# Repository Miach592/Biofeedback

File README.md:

View this project on [CADLAB.io](https://cadlab.io/project/1697). 

# Biofeedback

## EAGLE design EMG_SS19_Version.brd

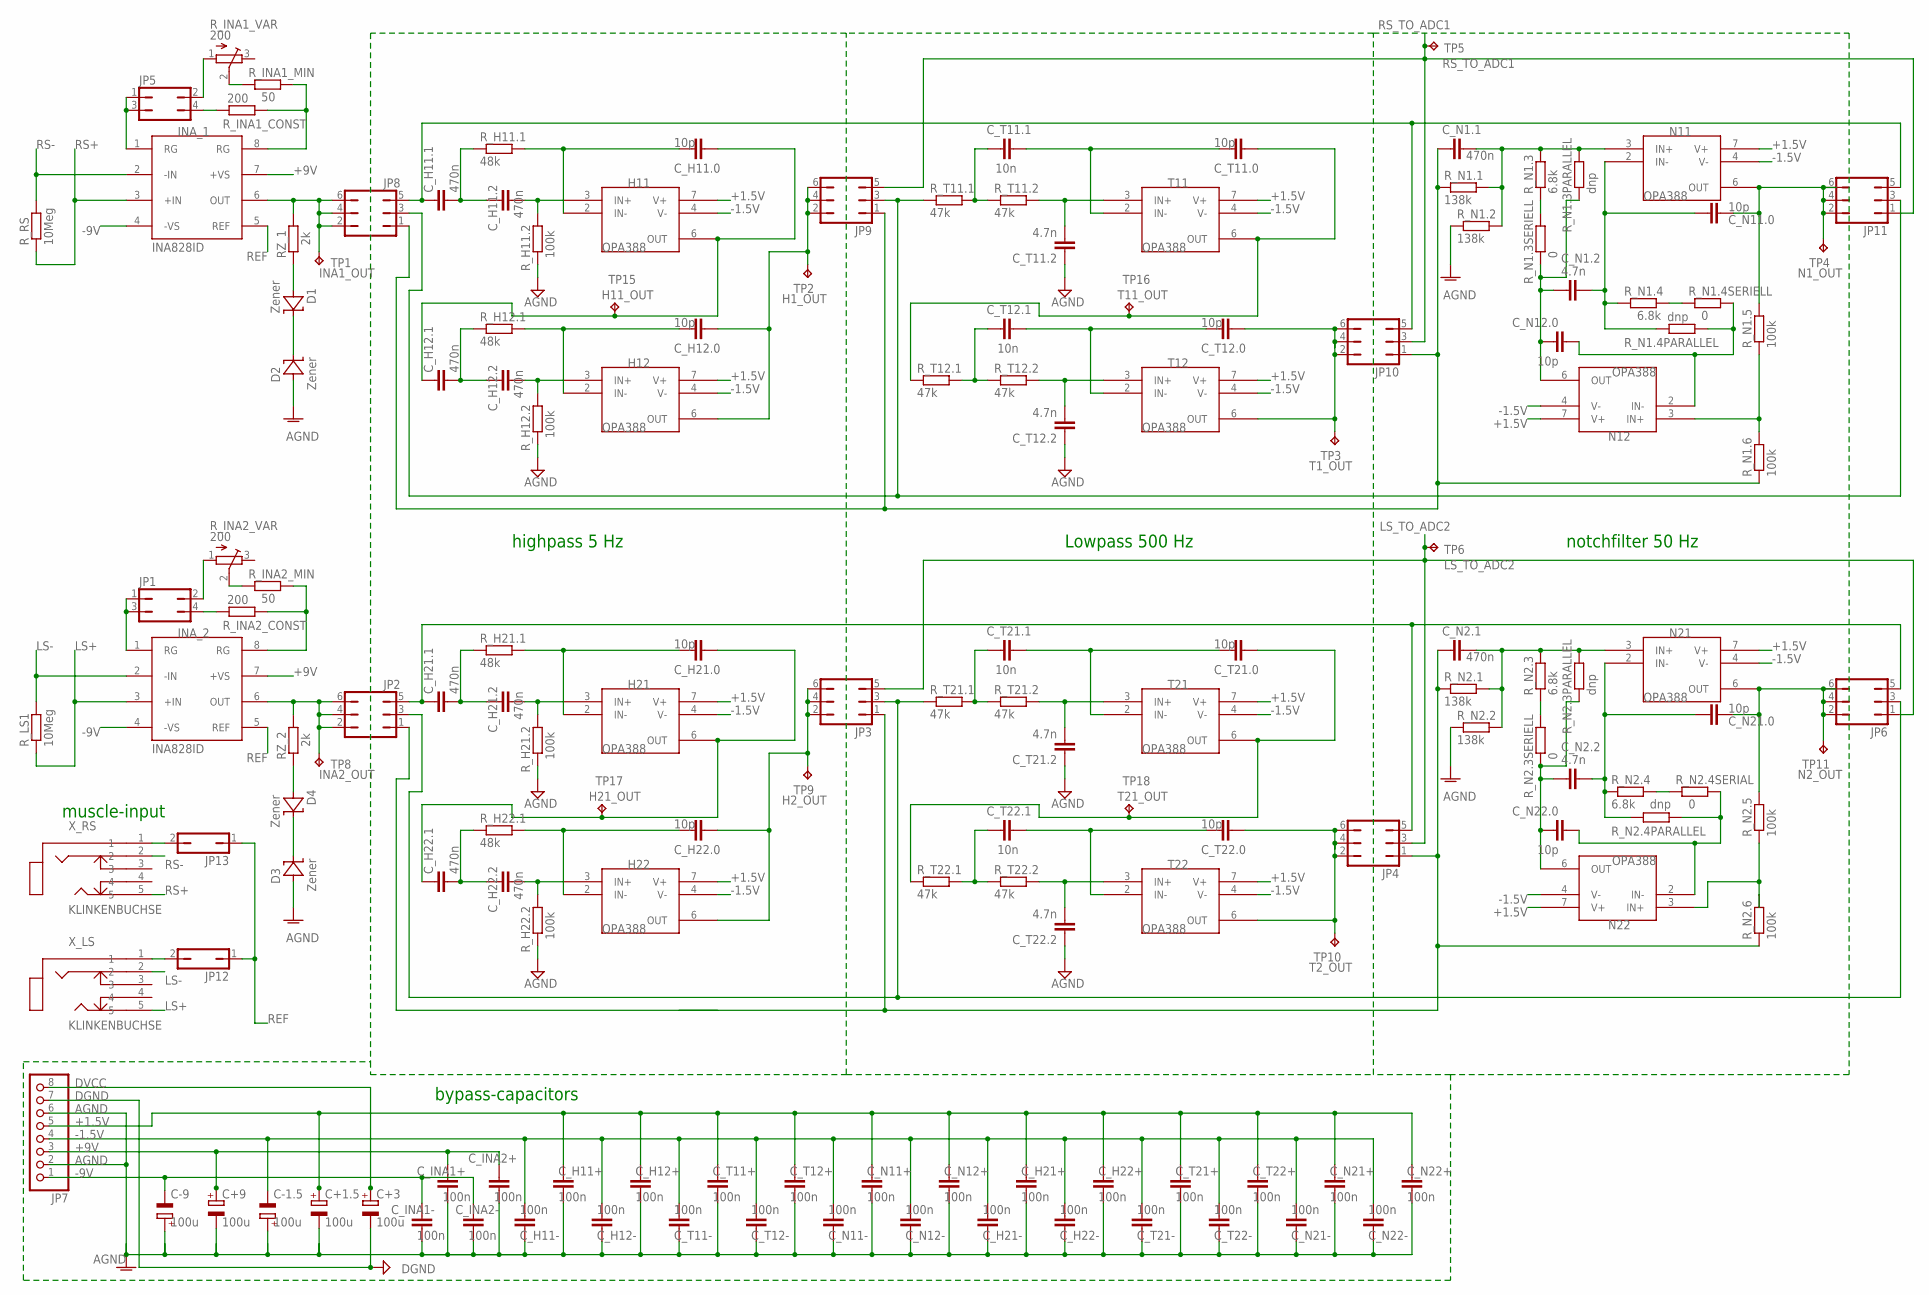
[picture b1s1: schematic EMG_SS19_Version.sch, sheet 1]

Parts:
C+1.5, C+3, C+9: 100u; RADIAL_SMD_ELKO_6_3
C-1.5, C-9: 100u; RADIAL_SMD_ELKO_6_3
C_H11+, C_H11-, C_H12+, C_H12-, C_H21+, C_H21-, C_H22+, C_H22-: 100n; C0805
C_H11.0, C_H12.0, C_H21.0, C_H22.0: 10p; C0805
C_H11.1, C_H11.2, C_H12.1, C_H12.2, C_H21.1, C_H21.2, C_H22.1, C_H22.2: 470n; C0805
C_INA1+, C_INA1-, C_INA2+, C_INA2-: 100n; C0805
C_N1.1, C_N2.1: 470n; C0805
C_N1.2, C_N2.2: 4.7n; C0805
C_N11+, C_N11-, C_N12+, C_N12-, C_N21+, C_N21-, C_N22+, C_N22-: 100n; C0805
C_N11.0, C_N12.0, C_N21.0, C_N22.0: 10p; C0805
C_T11+, C_T11-, C_T12+, C_T12-, C_T21+, C_T21-, C_T22+, C_T22-: 100n; C0805
C_T11.0, C_T12.0, C_T21.0, C_T22.0: 10p; C0805
C_T11.1, C_T12.1, C_T21.1, C_T22.1: 10n; C0805
C_T11.2, C_T12.2, C_T21.2, C_T22.2: 4.7n; C0805
D1, D2, D3, D4: Zener; SOT-23
H11, H12, H21, H22: OPA388; SOIC127P600X175-8N
INA_1, INA_2: INA828ID; SOIC8
JP1, JP5: JP2Q
JP2, JP3, JP4, JP6, JP8, JP9, JP10, JP11: JP3Q
JP7: PINHD-1X8; 1X08
JP12, JP13: JP1Q; JP1
N11, N12, N21, N22: OPA388; SOIC127P600X175-8N
RZ_1, RZ_2: 2k; R0805
R_H11.1, R_H12.1, R_H21.1, R_H22.1: 48k; R0805
R_H11.2, R_H12.2, R_H21.2, R_H22.2: 100k; R0805
R_INA1_CONST, R_INA2_CONST: 200; R0805
R_INA1_MIN, R_INA2_MIN: 50; R0805
R_INA1_VAR, R_INA2_VAR: 200; SM-42/43W
R_LS1: 10Meg; R0805
R_N1.1, R_N1.2, R_N2.1, R_N2.2: 138k; R0805
R_N1.3, R_N1.4, R_N2.3, R_N2.4: 6.8k; R0805
R_N1.3PARALLEL, R_N1.4PARALLEL, R_N2.3PARALLEL, R_N2.4PARALLEL: dnp; R0805
R_N1.3SERIELL, R_N1.4SERIELL, R_N2.3SERIELL, R_N2.4SERIAL: 0; R0805
R_N1.5, R_N1.6, R_N2.5, R_N2.6: 100k; R0805
R_RS: 10Meg; R0805
R_T11.1, R_T11.2, R_T12.1, R_T12.2, R_T21.1, R_T21.2, R_T22.1, R_T22.2: 47k; R0805
T11, T12, T21, T22: OPA388; SOIC127P600X175-8N
TP1, TP2, TP3, TP4, TP8, TP9, TP10, TP11, TP15, TP16, TP17, TP18: TPPAD1-13; P1-13
TP5: RS_TO_ADC; P1-13
TP6: LS_TO_ADC; P1-13
X_LS: KLINKENBUCHSE; FC68131-5P
X_RS: KLINKENBUCHSE; FC68131-5P

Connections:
+1.5V: C+1.5.+, C_H11+.1, C_H12+.1, C_H21+.1, C_H22+.1, C_N11+.1, C_N12+.1, C_N21+.1, C_N22+.1, C_T11+.1, C_T12+.1, C_T21+.1, C_T22+.1, H11.7 (V+), H12.7 (V+), H21.7 (V+), H22.7 (V+), JP7.5, N11.7 (V+), N12.7 (V+), N21.7 (V+), N22.7 (V+), T11.7 (V+), T12.7 (V+), T21.7 (V+), T22.7 (V+)
+9V: C+9.+, C_INA1+.1, C_INA2+.1, INA_1.7 (+VS), INA_2.7 (+VS), JP7.3
-1.5V: C-1.5.-, C_H11-.2, C_H12-.2, C_H21-.2, C_H22-.2, C_N11-.2, C_N12-.2, C_N21-.2, C_N22-.2, C_T11-.2, C_T12-.2, C_T21-.2, C_T22-.2, H11.4 (V-), H12.4 (V-), H21.4 (V-), H22.4 (V-), JP7.4, N11.4 (V-), N12.4 (V-), N21.4 (V-), N22.4 (V-), T11.4 (V-), T12.4 (V-), T21.4 (V-), T22.4 (V-)
-9V: C-9.-, C_INA1-.1, C_INA2-.1, INA_1.4 (-VS), INA_2.4 (-VS), JP7.1
AGND: C+1.5.-, C+9.-, C-1.5.+, C-9.+, C_H11+.2, C_H11-.1, C_H12+.2, C_H12-.1, C_H21+.2, C_H21-.1, C_H22+.2, C_H22-.1, C_INA1+.2, C_INA1-.2, C_INA2+.2, C_INA2-.2, C_N11+.2, C_N11-.1, C_N12+.2, C_N12-.1, C_N21+.2, C_N21-.1, C_N22+.2, C_N22-.1, C_T11+.2, C_T11-.1, C_T11.2.1, C_T12+.2, C_T12-.1, C_T12.2.1, C_T21+.2, C_T21-.1, C_T21.2.1, C_T22+.2, C_T22-.1, C_T22.2.1, D2.1 (A), D3.1 (A), JP7.2, JP7.6, R_H11.2.1, R_H12.2.1, R_H21.2.1, R_H22.2.1, R_N1.2.1, R_N2.2.1; also elsewhere on the board
DGND: C+3.-, JP7.7; also elsewhere on the board
DVCC: C+3.+, JP7.8; also elsewhere on the board
H1_OUT: C_H12.0.1, H12.6 (OUT), JP9.2, JP9.4, JP9.6, TP2.TP
H2_OUT: C_H22.0.1, H22.6 (OUT), JP3.2, JP3.4, JP3.6, TP9.TP
H11_OUT: C_H11.0.1, C_H12.1.1, H11.6 (OUT), TP15.TP
H21_OUT: C_H21.0.1, C_H22.1.1, H21.6 (OUT), TP17.TP
INA1_OUT: INA_1.6 (OUT), JP8.2, JP8.4, JP8.6, RZ_1.2, TP1.TP
INA2_OUT: INA_2.6 (OUT), JP2.2, JP2.4, JP2.6, RZ_2.2, TP8.TP
LS+: INA_2.3 (+IN), R_LS1.1, X_LS.5
LS-: INA_2.2 (-IN), R_LS1.2, X_LS.2
LS_TO_ADC2: JP3.5, JP4.3, JP6.1, TP6.TP; also elsewhere on the board
N1_OUT: C_N11.0.1, JP11.2, JP11.4, JP11.6, N11.6 (OUT), R_N1.5.2, TP4.TP
N2_OUT: C_N21.0.1, JP6.2, JP6.4, JP6.6, N21.6 (OUT), R_N2.5.2, TP11.TP
unnamed: R_INA2_MIN.1, R_INA2_VAR.2 (S)
unnamed: C_H11.1.2, C_H11.2.1, R_H11.1.1
unnamed: C_H11.2.2, H11.3 (IN+), R_H11.2.2
unnamed: D1.1 (A), RZ_1.1
unnamed: D1.3 (C), D2.3 (C)
unnamed: C_H12.1.2, C_H12.2.1, R_H12.1.1
unnamed: C_H12.2.2, H12.3 (IN+), R_H12.2.2
unnamed: C_T11.1.1, R_T11.1.2, R_T11.2.1
unnamed: C_H11.0.2, H11.2 (IN-), R_H11.1.2
unnamed: C_T11.2.2, R_T11.2.2, T11.3 (IN+)
unnamed: C_T12.1.1, R_T12.1.2, R_T12.2.1
unnamed: C_H12.0.2, H12.2 (IN-), R_H12.1.2
unnamed: C_T12.2.2, R_T12.2.2, T12.3 (IN+)
unnamed: C_T12.0.2, C_T12.1.2, T12.2 (IN-)
unnamed: JP5.4, R_INA1_CONST.1
unnamed: C_N1.1.2, N11.3 (IN+), R_N1.1.2, R_N1.2.2, R_N1.3.2, R_N1.3PARALLEL.2
unnamed: C_N1.2.1, C_N12.0.2, N12.6 (OUT), R_N1.3PARALLEL.1, R_N1.3SERIELL.1
unnamed: C_N1.2.2, C_N11.0.2, N11.2 (IN-), R_N1.4.1, R_N1.4PARALLEL.1
unnamed: C_N12.0.1, N12.2 (IN-), R_N1.4PARALLEL.2, R_N1.4SERIELL.2
unnamed: C_T11.0.2, C_T11.1.2, T11.2 (IN-)
unnamed: N12.3 (IN+), R_N1.5.1, R_N1.6.2
unnamed: C_H21.1.2, C_H21.2.1, R_H21.1.1
unnamed: C_H21.2.2, H21.3 (IN+), R_H21.2.2
unnamed: C_H22.1.2, C_H22.2.1, R_H22.1.1
unnamed: C_H22.2.2, H22.3 (IN+), R_H22.2.2
unnamed: C_T21.1.1, R_T21.1.2, R_T21.2.1
unnamed: C_T21.2.2, R_T21.2.2, T21.3 (IN+)
unnamed: C_T22.1.1, R_T22.1.2, R_T22.2.1
unnamed: C_T22.2.2, R_T22.2.2, T22.3 (IN+)
unnamed: C_N2.1.2, N21.3 (IN+), R_N2.1.2, R_N2.2.2, R_N2.3.2, R_N2.3PARALLEL.2
unnamed: C_N2.2.1, C_N22.0.2, N22.6 (OUT), R_N2.3PARALLEL.1, R_N2.3SERIELL.1
unnamed: C_N2.2.2, C_N21.0.2, N21.2 (IN-), R_N2.4.1, R_N2.4PARALLEL.1
unnamed: C_N22.0.1, N22.2 (IN-), R_N2.4PARALLEL.2, R_N2.4SERIAL.2
unnamed: N22.3 (IN+), R_N2.5.1, R_N2.6.2
unnamed: JP1.4, R_INA2_CONST.1
unnamed: JP1.2, R_INA2_VAR.1 (A)
unnamed: JP5.2, R_INA1_VAR.1 (A)
unnamed: C_H21.1.1, JP2.5, JP4.5, JP6.5
unnamed: C_H11.1.1, JP8.5, JP10.5, JP11.5
unnamed: JP2.3, JP3.3, JP6.3, R_T21.1.1
unnamed: C_N2.1.1, JP2.1, JP3.1, JP4.1, R_N2.1.1, R_N2.6.1
unnamed: JP8.3, JP9.3, JP11.3, R_T11.1.1
unnamed: C_N1.1.1, JP8.1, JP9.1, JP10.1, R_N1.1.1, R_N1.6.1
unnamed: D4.1 (A), RZ_2.1
unnamed: D3.3 (C), D4.3 (C)
unnamed: C_H21.0.2, H21.2 (IN-), R_H21.1.2
unnamed: R_INA1_MIN.1, R_INA1_VAR.2 (S)
unnamed: C_H22.0.2, H22.2 (IN-), R_H22.1.2
unnamed: C_T22.0.2, C_T22.1.2, T22.2 (IN-)
unnamed: C_T21.0.2, C_T21.1.2, T21.2 (IN-)
unnamed: JP12.2, X_LS.1
unnamed: JP13.2, X_RS.1
unnamed: R_N2.4.2, R_N2.4SERIAL.1
unnamed: R_N2.3.1, R_N2.3SERIELL.2
unnamed: R_N1.3.1, R_N1.3SERIELL.2
unnamed: R_N1.4.2, R_N1.4SERIELL.1
REF: INA_1.5 (REF), INA_2.5 (REF), JP12.1, JP13.1
RG1+: INA_1.1 (RG), JP5.1, JP5.3
RG1-: INA_1.8 (RG), R_INA1_CONST.2, R_INA1_MIN.2
RG2+: INA_2.1 (RG), JP1.1, JP1.3
RG2-: INA_2.8 (RG), R_INA2_CONST.2, R_INA2_MIN.2
RS+: INA_1.3 (+IN), R_RS.1, X_RS.5
RS-: INA_1.2 (-IN), R_RS.2, X_RS.2
RS_TO_ADC1: JP9.5, JP10.3, JP11.1, TP5.TP; also elsewhere on the board
T1_OUT: C_T12.0.1, JP10.2, JP10.4, JP10.6, T12.6 (OUT), TP3.TP
T2_OUT: C_T22.0.1, JP4.2, JP4.4, JP4.6, T22.6 (OUT), TP10.TP
T11_OUT: C_T11.0.1, R_T12.1.1, T11.6 (OUT), TP16.TP
T21_OUT: C_T21.0.1, R_T22.1.1, T21.6 (OUT), TP18.TP

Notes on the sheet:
highpass 5 Hz
Lowpass 500 Hz
notchfilter 50 Hz
bypass-capacitors
muscle-input

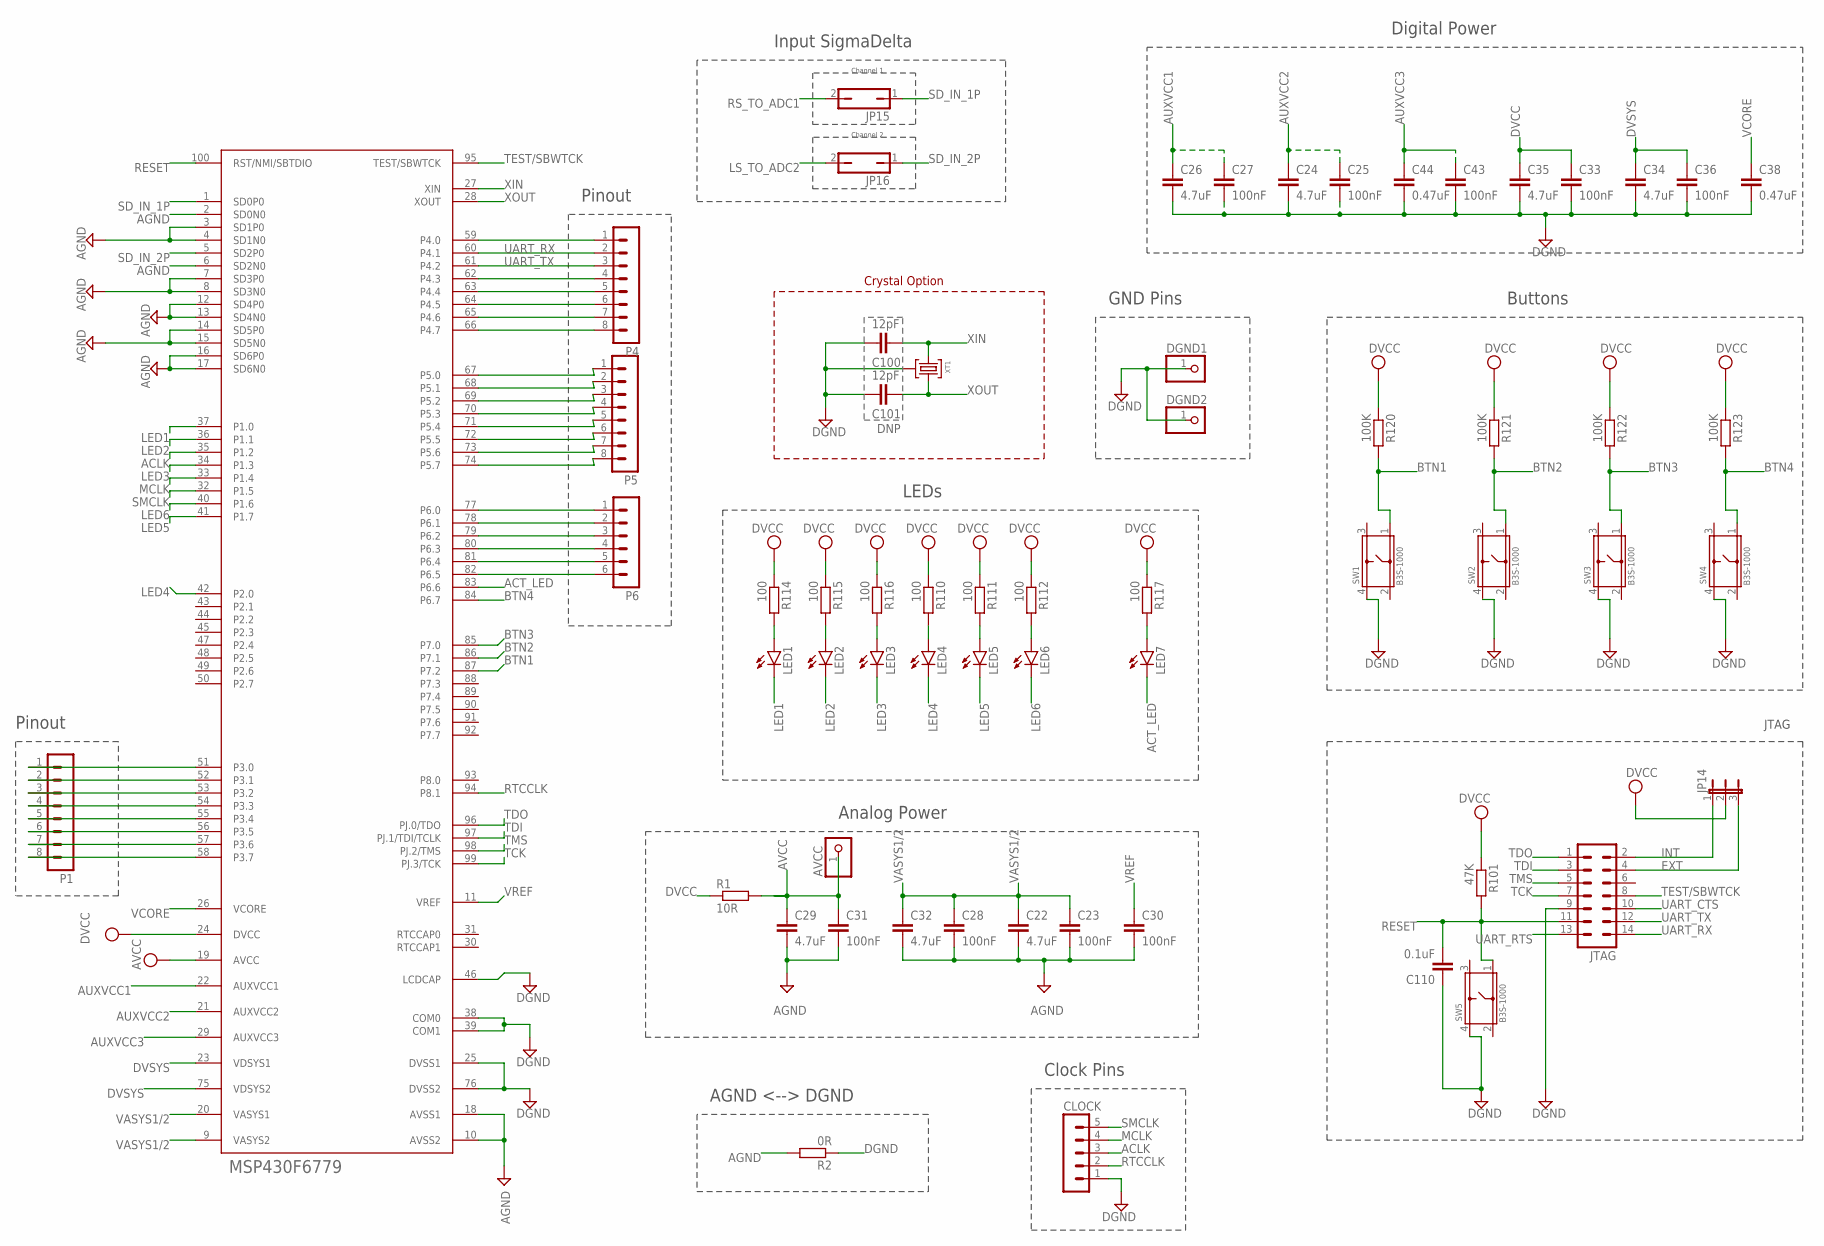
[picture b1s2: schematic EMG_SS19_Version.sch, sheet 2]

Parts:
AVCC: PINHD-1X1; 1X01
C22, C24, C26, C29, C32, C34, C35: 4.7uF; C0805
C23, C25, C27, C28, C30, C31, C33, C36, C43: 100nF; C0805
C38, C44: 0.47uF; C0805
C100, C101: 12pF; C0805
C110: 0.1uF; C0805
CLOCK: MA05-1
DGND1, DGND2: PINHD-1X1; 1X01
JP14: JP2E; JP2
JP15, JP16: JP1Q; JP1
JTAG: ML14
LED1, LED2, LED3, LED4, LED5, LED6, LED7: LEDCHIP-LED0805; CHIP-LED0805
P1, P4, P5: MA08-1
P6: MA06-1
R1: 10R; R0805
R2: 0R; R0805
R101: 47K; R0805
R110, R111, R112, R114, R115, R116, R117: 100; R0805
R120, R121, R122, R123: 100K; R0805
SW1, SW2, SW3, SW4, SW5: B3S-1000; SW_B3S-1000
U$1: MSP430F6779PZ; S-PQFP-G100(PZ)
XT1: CM200T

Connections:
ACLK: CLOCK.3, U$1.35 (P1.2)
ACT_LED: LED7.C, U$1.83 (P6.6)
AGND: C22.2, C23.2, C28.2, C29.2, C30.2, C31.2, C32.2, R2.2, U$1.2 (SD0N0), U$1.3 (SD1P0), U$1.4 (SD1N0), U$1.6 (SD2N0), U$1.7 (SD3P0), U$1.8 (SD3N0), U$1.10 (AVSS2), U$1.12 (SD4P0), U$1.13 (SD4N0), U$1.14 (SD5P0), U$1.15 (SD5N0), U$1.16 (SD6P0), U$1.17 (SD6N0), U$1.18 (AVSS1); also elsewhere on the board
AUXVCC1: C26.1, C27.1, U$1.22 (AUXVCC1)
AUXVCC2: C24.1, C25.1, U$1.21 (AUXVCC2)
AUXVCC3: C43.1, C44.1, U$1.29 (AUXVCC3)
AVCC: AVCC.1, C29.1, C31.1, R1.2, U$1.19 (AVCC)
BTN1: R120.2, SW1.1, U$1.87 (P7.2)
BTN2: R121.2, SW2.1, U$1.86 (P7.1)
BTN3: R122.2, SW3.1, U$1.85 (P7.0)
BTN4: R123.2, SW4.1, U$1.84 (P6.7)
DGND: C24.2, C25.2, C26.2, C27.2, C33.2, C34.2, C35.2, C36.2, C38.2, C43.2, C44.2, C100.2, C101.2, C110.1, CLOCK.1, DGND1.1, DGND2.1, JTAG.9, R2.1, SW1.4, SW2.4, SW3.4, SW4.4, SW5.4, U$1.25 (DVSS1), U$1.38 (COM0), U$1.39 (COM1), U$1.46 (LCDCAP), U$1.76 (DVSS2), XT1.P3 (3); also elsewhere on the board
DVCC: C33.1, C35.1, JP14.2, R1.1, R101.1, R110.1, R111.1, R112.1, R114.1, R115.1, R116.1, R117.1, R120.1, R121.1, R122.1, R123.1, U$1.24 (DVCC); also elsewhere on the board
DVSYS: C34.1, C36.1, U$1.23 (VDSYS1), U$1.75 (VDSYS2)
EXT: JP14.3, JTAG.4
INT: JP14.1, JTAG.2
LED1: LED1.C, U$1.37 (P1.0)
LED2: LED2.C, U$1.36 (P1.1)
LED3: LED3.C, U$1.34 (P1.3)
LED4: LED4.C, U$1.42 (P2.0)
LED5: LED5.C, U$1.41 (P1.7)
LED6: LED6.C, U$1.40 (P1.6)
LS_TO_ADC2: JP16.2; also elsewhere on the board
MCLK: CLOCK.4, U$1.33 (P1.4)
unnamed: LED1.A, R114.2
unnamed: LED2.A, R115.2
unnamed: LED3.A, R116.2
unnamed: LED7.A, R117.2
unnamed: LED4.A, R110.2
unnamed: LED5.A, R111.2
unnamed: LED6.A, R112.2
unnamed: P1.1, U$1.51 (P3.0)
unnamed: P1.2, U$1.52 (P3.1)
unnamed: P1.3, U$1.53 (P3.2)
unnamed: P1.4, U$1.54 (P3.3)
unnamed: P1.5, U$1.55 (P3.4)
unnamed: P1.6, U$1.56 (P3.5)
unnamed: P1.7, U$1.57 (P3.6)
unnamed: P1.8, U$1.58 (P3.7)
unnamed: P5.1, U$1.67 (P5.0)
unnamed: P5.2, U$1.68 (P5.1)
unnamed: P5.3, U$1.69 (P5.2)
unnamed: P5.4, U$1.70 (P5.3)
unnamed: P5.5, U$1.71 (P5.4)
unnamed: P5.6, U$1.72 (P5.5)
unnamed: P5.7, U$1.73 (P5.6)
unnamed: P5.8, U$1.74 (P5.7)
unnamed: P4.5, U$1.63 (P4.4)
unnamed: P6.2, U$1.78 (P6.1)
unnamed: P6.1, U$1.77 (P6.0)
P4.0: P4.1, U$1.59 (P4.0)
P4.3: P4.4, U$1.62 (P4.3)
P4.5: P4.6, U$1.64 (P4.5)
P4.6: P4.7, U$1.65 (P4.6)
P4.7: P4.8, U$1.66 (P4.7)
P6.2: P6.3, U$1.79 (P6.2)
P6.3: P6.4, U$1.80 (P6.3)
P6.4: P6.5, U$1.81 (P6.4)
P6.5: P6.6, U$1.82 (P6.5)
RESET: C110.2, JTAG.11, R101.2, SW5.1, U$1.100 (RST/NMI/SBTDIO)
RS_TO_ADC1: JP15.2; also elsewhere on the board
RTCCLK: CLOCK.2, U$1.94 (P8.1)
SD_IN_1P: JP15.1, U$1.1 (SD0P0)
SD_IN_2P: JP16.1, U$1.5 (SD2P0)
SMCLK: CLOCK.5, U$1.32 (P1.5)
TCK: JTAG.7, U$1.99 (PJ.3/TCK)
TDI: JTAG.3, U$1.97 (PJ.1/TDI/TCLK)
TDO: JTAG.1, U$1.96 (PJ.0/TDO)
TEST/SBWTCK: JTAG.8, U$1.95 (TEST/SBWTCK)
TMS: JTAG.5, U$1.98 (PJ.2/TMS)
UART_CTS: JTAG.10
UART_RTS: JTAG.13
UART_RX: JTAG.14, P4.2, U$1.60 (P4.1)
UART_TX: JTAG.12, P4.3, U$1.61 (P4.2)
VASYS1/2: C22.1, C23.1, C28.1, C32.1, U$1.9 (VASYS2), U$1.20 (VASYS1)
VCORE: C38.1, U$1.26 (VCORE)
VREF: C30.1, U$1.11 (VREF)
XIN: C100.1, U$1.27 (XIN), XT1.P2 (2)
XOUT: C101.1, U$1.28 (XOUT), XT1.P1 (1)

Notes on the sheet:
JTAG
Crystal Option
Buttons
DNP
Clock Pins
LEDs
Digital Power
Analog Power
Pinout
AGND <--> DGND
Input SigmaDelta
Channel 1
Channel 2
GND Pins

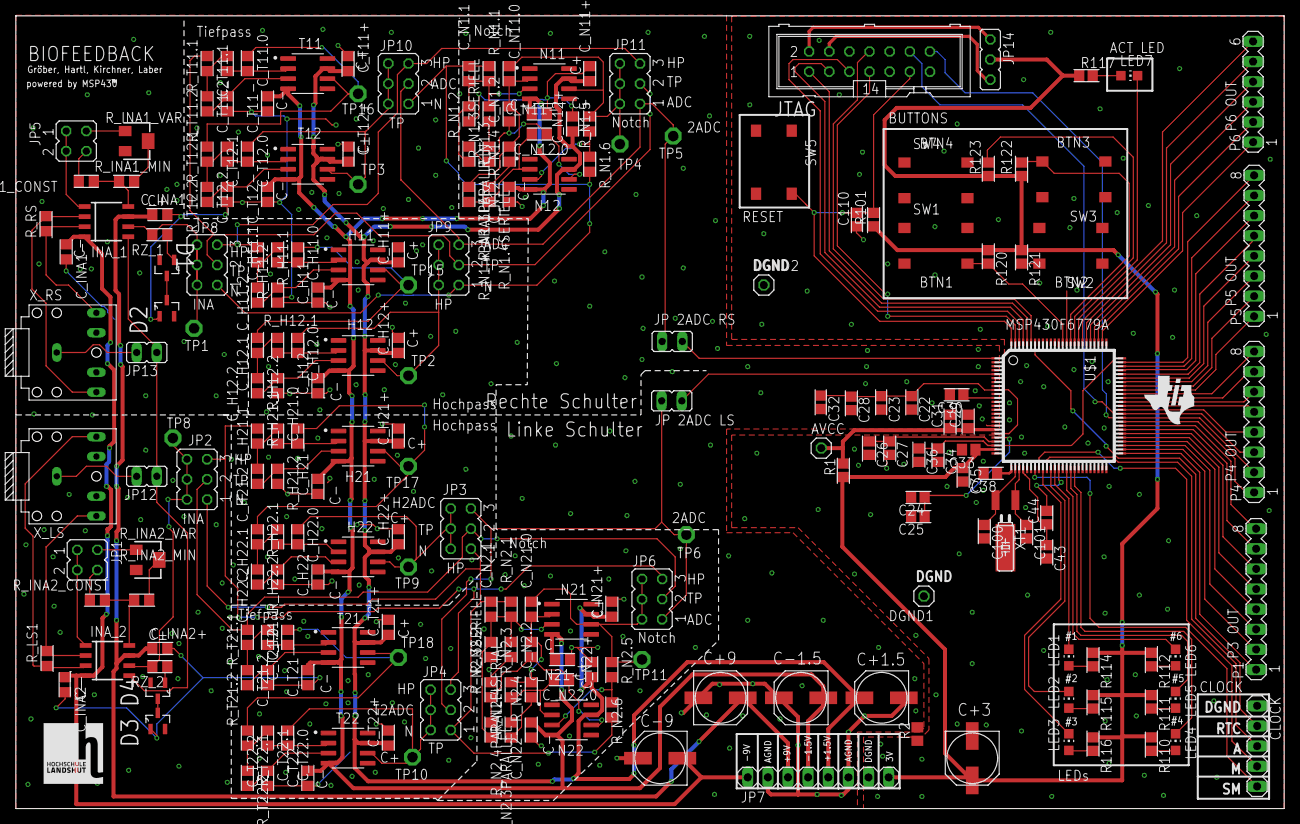
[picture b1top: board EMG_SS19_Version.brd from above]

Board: 2 copper layers, 160.0 x 100.0 mm, 219 parts (0 on the bottom side), 158 nets.

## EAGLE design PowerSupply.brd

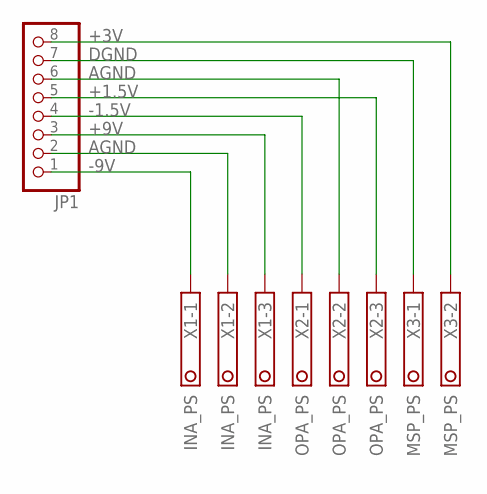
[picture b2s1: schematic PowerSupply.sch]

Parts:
JP1: PINHD-1X8; 1X08
X1: INA_PS; 1751251
X2: OPA_PS; 1751251
X3: MSP_PS; 1751248

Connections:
+1.5V: JP1.5, X2.3
+3V: JP1.8, X3.2
+9V: JP1.3, X1.3
-1.5V: JP1.4, X2.1
-9V: JP1.1, X1.1
AGND: JP1.2, JP1.6, X1.2, X2.2
DGND: JP1.7, X3.1

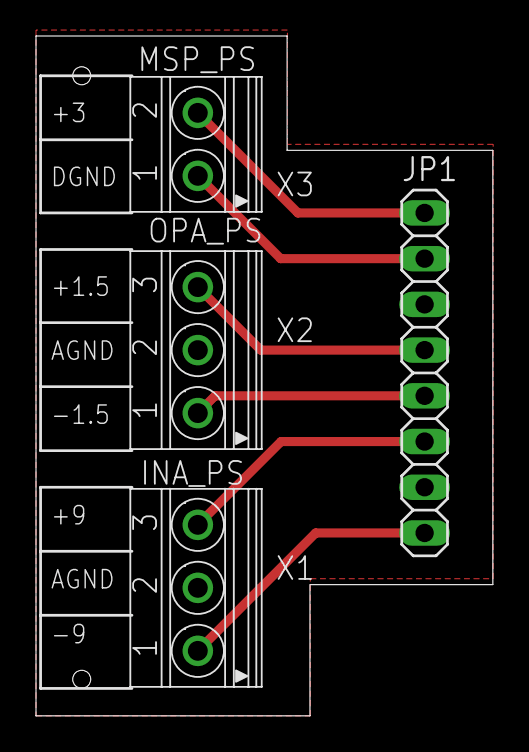
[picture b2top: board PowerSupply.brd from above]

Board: 2 copper layers, 25.4 x 37.8 mm, 4 parts (0 on the bottom side), 7 nets.

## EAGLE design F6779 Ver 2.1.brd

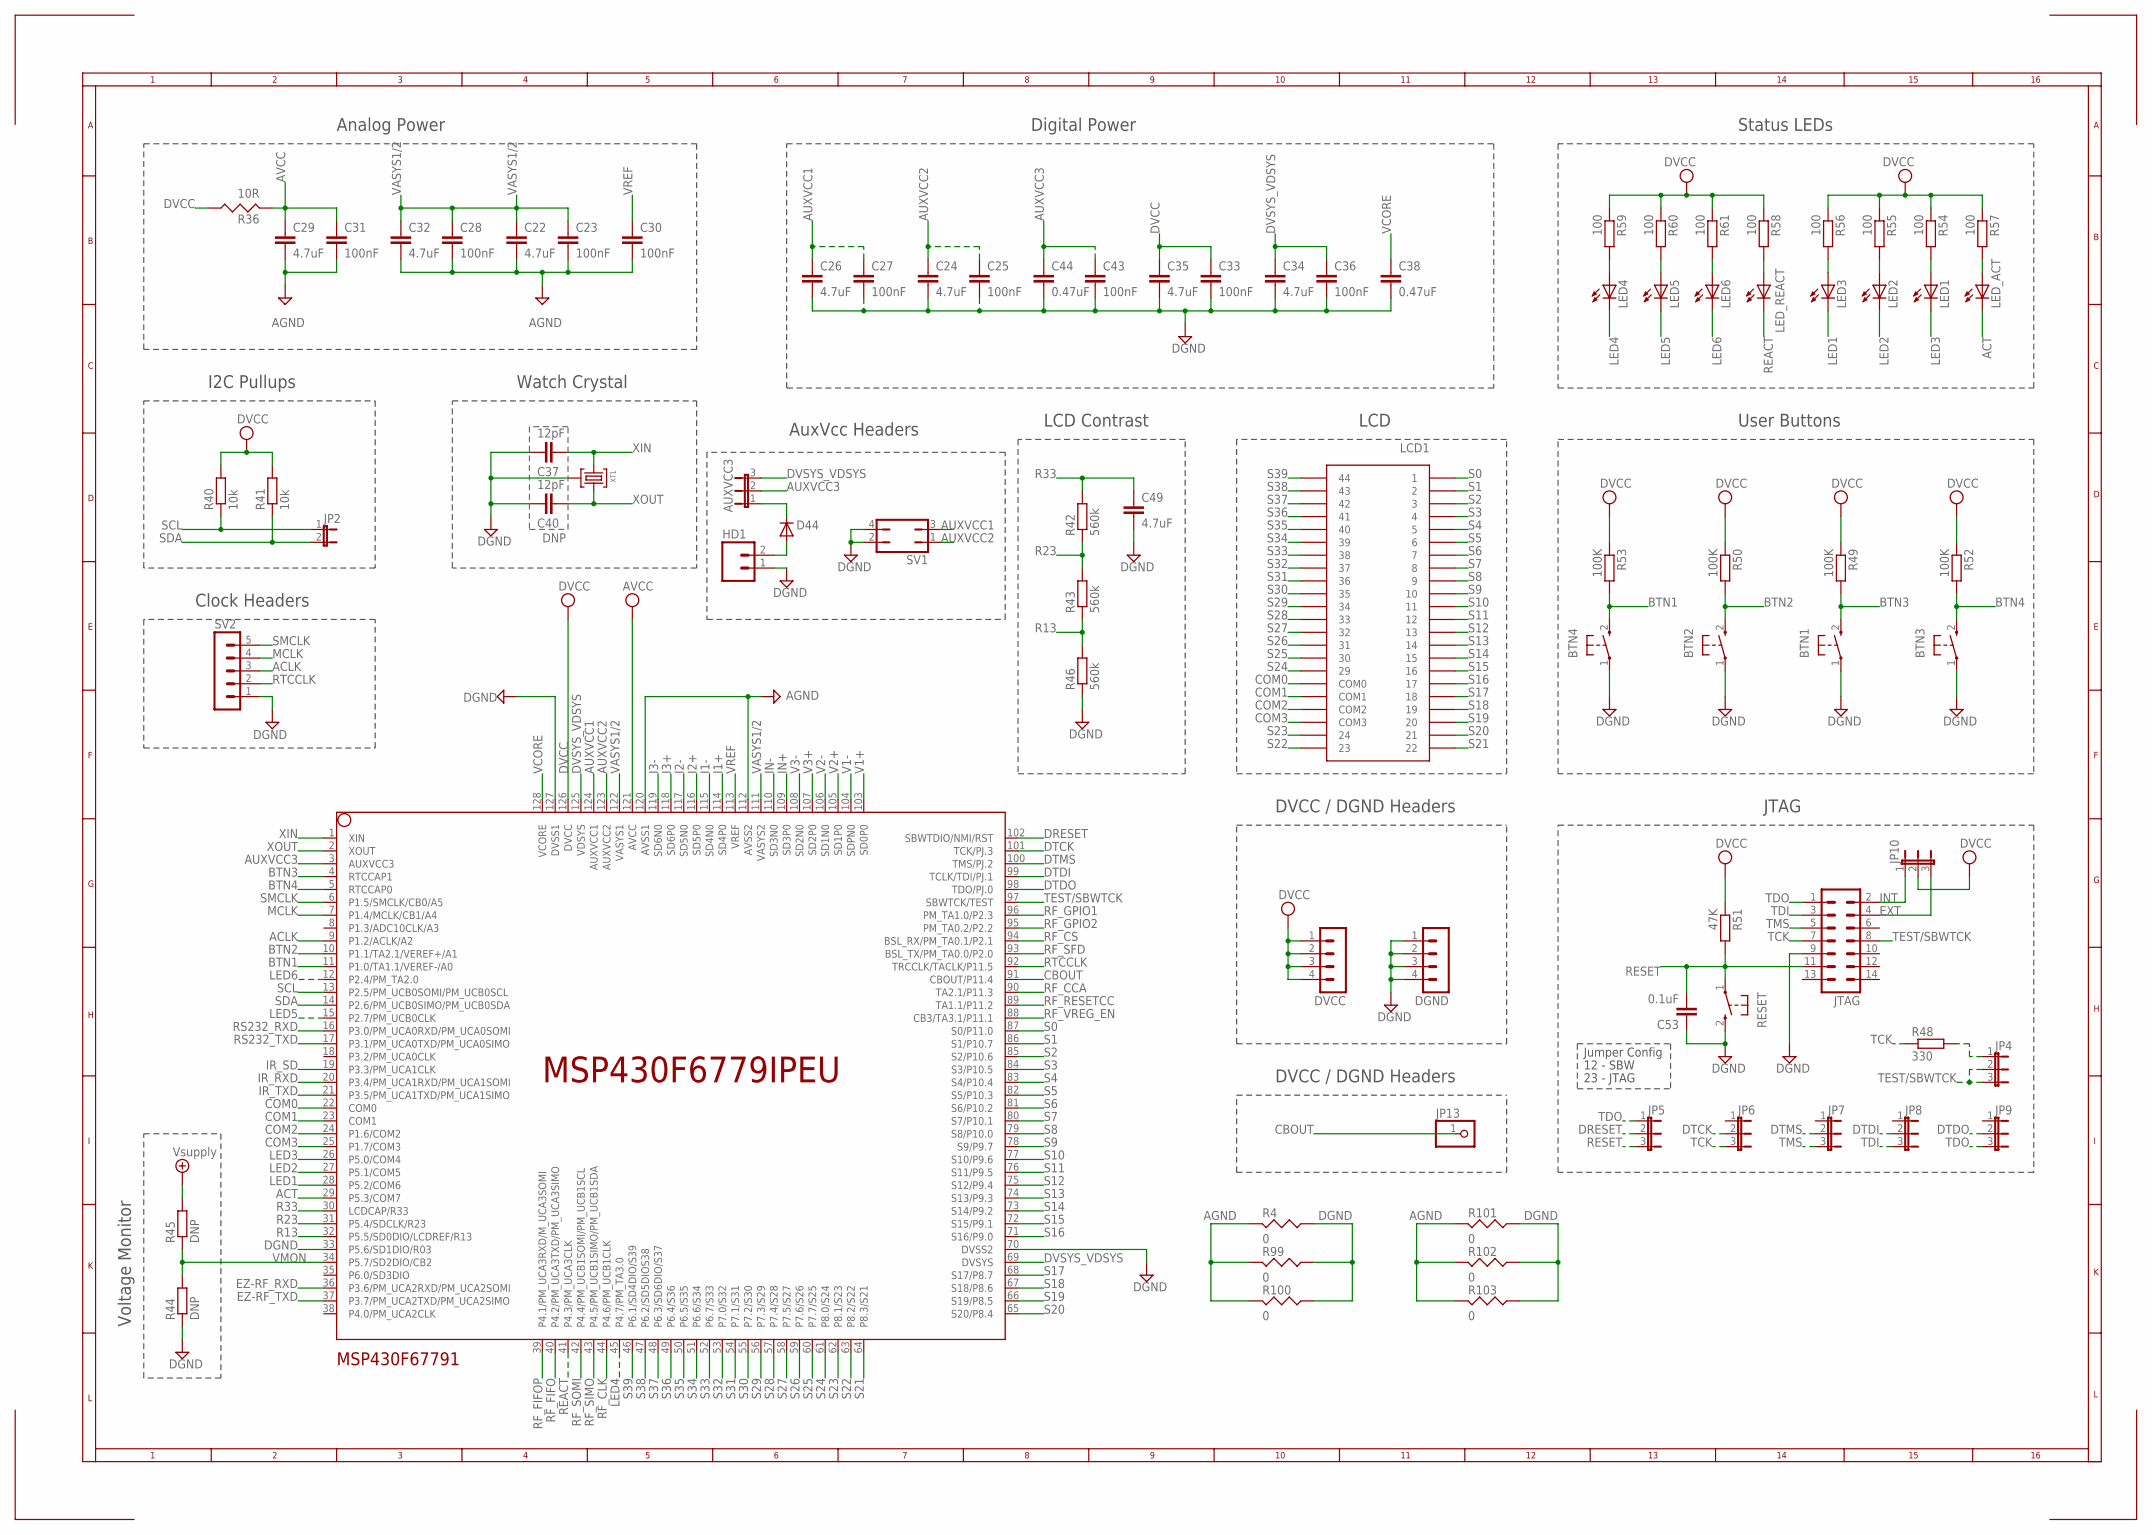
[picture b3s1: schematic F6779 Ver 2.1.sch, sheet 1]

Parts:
AUXVCC3: JP2E; JP2
BTN1, BTN2, BTN3, BTN4: PB; PBTH
C22, C24, C26, C29, C32, C34, C35, C49: 4.7uF; C0603
C23, C25, C27, C28, C30, C31, C33, C36, C43: 100nF; C0603
C37, C40: 12pF; C0603
C38, C44: 0.47uF; C0603
C53: 0.1uF; C0603
D44: PMLL4148; SOD80C
DGND: MA04-1
DVCC: MA04-1
HD1: M02PTH; 1X02
JP2: JP1E; JP1
JP4, JP5, JP6, JP7, JP8, JP9, JP10: JP2E; JP2
JP13: PINHD-1X1; 1X01
JTAG: ML14
LCD1: TI_160SEG_LCD
LED1, LED2, LED3, LED4, LED5, LED6: LED3MM
LED_ACT: LED3MM
LED_REACT: LED3MM
MSP430F67791: MSP430F6779IPEU; PEU128
R4, R99, R100, R101, R102, R103: 0; R0805
R36: 10R; R0805
R40, R41: 10k; R0603
R42, R43, R46: 560k; R0603
R44, R45: DNP; R0603
R48: 330; R0603
R49, R50, R52, R53: 100K; R0603
R51: 47K; R0603
R54, R55, R56, R57, R58, R59, R60, R61: 100; R0603
RESET: PB; PBTH
SV1: JP2Q
SV2: MA05-1
XT1: CM200T

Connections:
ACLK: MSP430F67791.9 (P1.2/ACLK/A2), SV2.3
ACT: LED_ACT.K (C), MSP430F67791.29 (P5.3/COM7); also elsewhere on the board
AGND: C22.2, C23.2, C28.2, C29.2, C30.2, C31.2, C32.2, MSP430F67791.112 (AVSS2), MSP430F67791.120 (AVSS1), R4.2, R99.2, R100.2, R101.2, R102.2, R103.2; also elsewhere on the board
AUXVCC1: C26.1, C27.1, MSP430F67791.124 (AUXVCC1), SV1.3
AUXVCC2: C24.1, C25.1, MSP430F67791.123 (AUXVCC2), SV1.1
AUXVCC3: AUXVCC3.2, C43.1, C44.1, MSP430F67791.3 (AUXVCC3)
AVCC: C29.1, C31.1, MSP430F67791.121 (AVCC), R36.2; also elsewhere on the board
BTN1: BTN4.2 (S), MSP430F67791.11 (P1.0/TA1.1/VEREF-/A0), R53.2
BTN2: BTN2.2 (S), MSP430F67791.10 (P1.1/TA2.1/VEREF+/A1), R50.2
BTN3: BTN1.2 (S), MSP430F67791.4 (RTCCAP1), R49.2
BTN4: BTN3.2 (S), MSP430F67791.5 (RTCCAP0), R52.2
CBOUT: JP13.1, MSP430F67791.91 (CBOUT/P11.4)
COM0: LCD1.COM0, MSP430F67791.22 (COM0)
COM1: LCD1.COM1, MSP430F67791.23 (COM1)
COM2: LCD1.COM2, MSP430F67791.24 (P1.6/COM2)
COM3: LCD1.COM3, MSP430F67791.25 (P1.7/COM3)
DGND: BTN1.1, BTN2.1, BTN3.1, BTN4.1, C24.2, C25.2, C26.2, C27.2, C33.2, C34.2, C35.2, C36.2, C37.2, C38.2, C40.2, C43.2, C44.2, C49.2, C53.1, DGND.1, DGND.2, DGND.3, DGND.4, HD1.1, JTAG.9, MSP430F67791.33 (P5.6/SD1DIO/R03), MSP430F67791.70 (DVSS2), MSP430F67791.127 (DVSS1), R4.1, R44.1, R46.1, R99.1, R100.1, R101.1, R102.1, R103.1, RESET.2 (S), SV1.2, SV1.4, SV2.1, XT1.P3 (3); also elsewhere on the board
DRESET: JP5.2, MSP430F67791.102 (SBWTDIO/NMI/RST)
DTCK: JP6.2, MSP430F67791.101 (TCK/PJ.3)
DTDI: JP8.2, MSP430F67791.99 (TCLK/TDI/PJ.1)
DTDO: JP9.2, MSP430F67791.98 (TDO/PJ.0)
DTMS: JP7.2, MSP430F67791.100 (TMS/PJ.2)
DVCC: C33.1, C35.1, DVCC.1, DVCC.2, DVCC.3, DVCC.4, JP10.2, MSP430F67791.126 (DVCC), R36.1, R40.2, R41.2, R49.1, R50.1, R51.1, R52.1, R53.1, R54.1, R55.1, R56.1, R57.1, R58.1, R59.1, R60.1, R61.1; also elsewhere on the board
DVSYS_VDSYS: AUXVCC3.3, C34.1, C36.1, MSP430F67791.69 (DVSYS), MSP430F67791.125 (VDSYS)
EXT: JP10.3, JTAG.4
EZ-RF_RXD: MSP430F67791.36 (P3.6/PM_UCA2RXD/PM_UCA2SOMI); also elsewhere on the board
EZ-RF_TXD: MSP430F67791.37 (P3.7/PM_UCA2TXD/PM_UCA2SIMO); also elsewhere on the board
I1+: MSP430F67791.114 (SD4P0); also elsewhere on the board
I1-: MSP430F67791.115 (SD4N0); also elsewhere on the board
I2+: MSP430F67791.116 (SD5P0); also elsewhere on the board
I2-: MSP430F67791.117 (SD5N0); also elsewhere on the board
I3+: MSP430F67791.118 (SD6P0); also elsewhere on the board
I3-: MSP430F67791.119 (SD6N0); also elsewhere on the board
IN+: MSP430F67791.109 (SD3P0); also elsewhere on the board
IN-: MSP430F67791.110 (SD3N0); also elsewhere on the board
INT: JP10.1, JTAG.2
IR_RXD: MSP430F67791.20 (P3.4/PM_UCA1RXD/PM_UCA1SOMI); also elsewhere on the board
IR_SD: MSP430F67791.19 (P3.3/PM_UCA1CLK); also elsewhere on the board
IR_TXD: MSP430F67791.21 (P3.5/PM_UCA1TXD/PM_UCA1SIMO); also elsewhere on the board
LED1: LED3.K (C), MSP430F67791.28 (P5.2/COM6)
LED2: LED2.K (C), MSP430F67791.27 (P5.1/COM5)
LED3: LED1.K (C), MSP430F67791.26 (P5.0/COM4)
LED4: LED4.K (C), MSP430F67791.45 (P4.7/PM_TA3.0)
LED5: LED5.K (C), MSP430F67791.15 (P2.7/PM_UCB0CLK)
LED6: LED6.K (C), MSP430F67791.12 (P2.4/PM_TA2.0)
MCLK: MSP430F67791.7 (P1.4/MCLK/CB1/A4), SV2.4
unnamed: LED3.A, R56.2
unnamed: AUXVCC3.1, D44.C
unnamed: LED2.A, R55.2
unnamed: JP4.1, R48.2
unnamed: LED4.A, R59.2
unnamed: LED5.A, R60.2
unnamed: LED1.A, R54.2
unnamed: LED6.A, R61.2
unnamed: LED_REACT.A, R58.2
unnamed: LED_ACT.A, R57.2
unnamed: D44.A, HD1.2
R13: MSP430F67791.32 (P5.5/SD0DIO/LCDREF/R13), R43.1, R46.2
R23: MSP430F67791.31 (P5.4/SDCLK/R23), R42.1, R43.2
R33: C49.1, MSP430F67791.30 (LCDCAP/R33), R42.2
REACT: LED_REACT.K (C), MSP430F67791.41 (P4.3/PM_UCA3CLK); also elsewhere on the board
RESET: C53.2, JP5.3, JTAG.11, R51.2, RESET.1
RF_CCA: MSP430F67791.90 (TA2.1/P11.3); also elsewhere on the board
RF_CLK: MSP430F67791.44 (P4.6/PM_UCB1CLK); also elsewhere on the board
RF_CS: MSP430F67791.94 (BSL_RX/PM_TA0.1/P2.1); also elsewhere on the board
RF_FIFO: MSP430F67791.40 (P4.2/PM_UCA3TXD/PM_UCA3SIMO); also elsewhere on the board
RF_FIFOP: MSP430F67791.39 (P4.1/PM_UCA3RXD/M_UCA3SOMI); also elsewhere on the board
RF_GPIO1: MSP430F67791.96 (PM_TA1.0/P2.3); also elsewhere on the board
RF_GPIO2: MSP430F67791.95 (PM_TA0.2/P2.2); also elsewhere on the board
RF_RESETCC: MSP430F67791.89 (TA1.1/P11.2); also elsewhere on the board
RF_SFD: MSP430F67791.93 (BSL_TX/PM_TA0.0/P2.0); also elsewhere on the board
RF_SIMO: MSP430F67791.43 (P4.5/PM_UCB1SIMO/PM_UCB1SDA); also elsewhere on the board
RF_SOMI: MSP430F67791.42 (P4.4/PM_UCB1SOMI/PM_UCB1SCL); also elsewhere on the board
RF_VREG_EN: MSP430F67791.88 (CB3/TA3.1/P11.1); also elsewhere on the board
RS232_RXD: MSP430F67791.16 (P3.0/PM_UCA0RXD/PM_UCA0SOMI); also elsewhere on the board
RS232_TXD: MSP430F67791.17 (P3.1/PM_UCA0TXD/PM_UCA0SIMO); also elsewhere on the board
RTCCLK: MSP430F67791.92 (TRCCLK/TACLK/P11.5), SV2.2
S0: LCD1.1, MSP430F67791.87 (S0/P11.0)
S1: LCD1.2, MSP430F67791.86 (S1/P10.7)
S2: LCD1.3, MSP430F67791.85 (S2/P10.6)
S3: LCD1.4, MSP430F67791.84 (S3/P10.5)
S4: LCD1.5, MSP430F67791.83 (S4/P10.4)
S5: LCD1.6, MSP430F67791.82 (S5/P10.3)
S6: LCD1.7, MSP430F67791.81 (S6/P10.2)
S7: LCD1.8, MSP430F67791.80 (S7/P10.1)
S8: LCD1.9, MSP430F67791.79 (S8/P10.0)
S9: LCD1.10, MSP430F67791.78 (S9/P9.7)
S10: LCD1.11, MSP430F67791.77 (S10/P9.6)
S11: LCD1.12, MSP430F67791.76 (S11/P9.5)
S12: LCD1.13, MSP430F67791.75 (S12/P9.4)
S13: LCD1.14, MSP430F67791.74 (S13/P9.3)
S14: LCD1.15, MSP430F67791.73 (S14/P9.2)
S15: LCD1.16, MSP430F67791.72 (S15/P9.1)
S16: LCD1.17, MSP430F67791.71 (S16/P9.0)
S17: LCD1.18, MSP430F67791.68 (S17/P8.7)
S18: LCD1.19, MSP430F67791.67 (S18/P8.6)
S19: LCD1.20, MSP430F67791.66 (S19/P8.5)
S20: LCD1.21, MSP430F67791.65 (S20/P8.4)
S21: LCD1.22, MSP430F67791.64 (P8.3/S21)
S22: LCD1.23, MSP430F67791.63 (P8.2/S22)
S23: LCD1.24, MSP430F67791.62 (P8.1/S23)
S24: LCD1.29, MSP430F67791.61 (P8.0/S24)
S25: LCD1.30, MSP430F67791.60 (P7.7/S25)
S26: LCD1.31, MSP430F67791.59 (P7.6/S26)
S27: LCD1.32, MSP430F67791.58 (P7.5/S27)
S28: LCD1.33, MSP430F67791.57 (P7.4/S28)
S29: LCD1.34, MSP430F67791.56 (P7.3/S29)
S30: LCD1.35, MSP430F67791.55 (P7.2/S30)
S31: LCD1.36, MSP430F67791.54 (P7.1/S31)
S32: LCD1.37, MSP430F67791.53 (P7.0/S32)
S33: LCD1.38, MSP430F67791.52 (P6.7/S33)
S34: LCD1.39, MSP430F67791.51 (P6.6/S34)
S35: LCD1.40, MSP430F67791.50 (P6.5/S35)
S36: LCD1.41, MSP430F67791.49 (P6.4/S36)
S37: LCD1.42, MSP430F67791.48 (P6.3/SD6DIO/S37)
S38: LCD1.43, MSP430F67791.47 (P6.2/SD5DIOS38)
S39: LCD1.44, MSP430F67791.46 (P6.1/SD4DIO/S39)
SCL: JP2.1, MSP430F67791.13 (P2.5/PM_UCB0SOMI/PM_UCB0SCL), R40.1; also elsewhere on the board
SDA: JP2.2, MSP430F67791.14 (P2.6/PM_UCB0SIMO/PM_UCB0SDA), R41.1; also elsewhere on the board
SMCLK: MSP430F67791.6 (P1.5/SMCLK/CB0/A5), SV2.5
TCK: JP6.3, JTAG.7, R48.1
TDI: JP8.3, JTAG.3
TDO: JP5.1, JP9.3, JTAG.1
TEST/SBWTCK: JP4.2, JP4.3, JTAG.8, MSP430F67791.97 (SBWTCK/TEST)
TMS: JP7.3, JTAG.5
V1+: MSP430F67791.103 (SD0P0); also elsewhere on the board
V1-: MSP430F67791.104 (SDPN0); also elsewhere on the board
V2+: MSP430F67791.105 (SD1P0); also elsewhere on the board
V2-: MSP430F67791.106 (SD1N0); also elsewhere on the board
V3+: MSP430F67791.107 (SD2P0); also elsewhere on the board
V3-: MSP430F67791.108 (SD2N0); also elsewhere on the board
VASYS1/2: C22.1, C23.1, C28.1, C32.1, MSP430F67791.111 (VASYS2), MSP430F67791.122 (VASYS1)
VCORE: C38.1, MSP430F67791.128 (VCORE)
VMON: MSP430F67791.34 (P5.7/SD2DIO/CB2), R44.2, R45.1
VREF: C30.1, MSP430F67791.113 (VREF)
VSUPPLY: R45.2; also elsewhere on the board
XIN: C37.1, MSP430F67791.1 (XIN), XT1.P2 (2)
XOUT: C40.1, MSP430F67791.2 (XOUT), XT1.P1 (1)

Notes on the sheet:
DNP
Clock Headers
AuxVcc Headers
LCD Contrast
Watch Crystal
Analog Power
Digital Power
Voltage Monitor
Status LEDs
User Buttons
LCD
I2C Pullups
JTAG
23 - JTAG
12 - SBW
Jumper Config
DVCC / DGND Headers
